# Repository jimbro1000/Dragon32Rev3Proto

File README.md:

# DRAGON 32 RECREATION Rev 3 #

This project started as a recreation of the SA2120 CPU Mainboard
for the 1982 Dragon Data **Dragon 32**

Everything (excluding modifications) is taken from the SA2120
schematics. Where this version changes is the move to surface
mount components which radically alters the size of each part
along with a move to using SRAM instead of DRAM. The intention
is that the board should be supplied fully or semi-populated
leaving just optional (socketed) components to be fitted.

The ROM is now a single 28C256 eprom with an option to switch
between two images using JP6 or to allow the rom to be
automatically selected from the PIA. In effect this allows the
computer to operate as a D32 but with two different images or
as a D64.

The video circuits have been isolated from the rest of the
board to improve output quality.

To maintain compatibility with the D64 there is an optional
serial port. This needs to be enabled by bridging a solder
jumper (JP3) to position 1-2. If the serial port is not
being populated it should be position 2-3. By default this
is not bridged and the computer will not function without
the jumper being set. If the supporting SMD ICs at U13 and
U14 are fitted the jumper can safely be left in position
1-2 regardless of whether the 6551 UART chip is fitting.

If you are fitting the board into an
early D32 case the serial port would be completely covered
without modifying the case. Later D32 cases had all four
ports but the fourth (serial) port blanked off internally.

A second (internal) cartridge port has been added, by way of
a 2x20 header, along with an additional +5V/Gnd pickup point
for further internal expansion. The keyboard connector also
has two additional pins that can supply 5v to the keyboard,
the extra pins are on the left. The keyboard should always 
be fitted to the right to avoid any shorts.

The board incorporates a replacement to the SAM chip based on
Ciaran Anscomb's SAMx4 design which in turn includes Stewart
Orchards 256k banker board 
<https://gitlab.com/sorchard001/dragon-256k-banker-board>

A custom VHDL is needed for this. Do not use the code from
Ciaran's site as it won't work.

The VHDL has potential (untried as of yet) to allow the
board to run permanently at double speed without loss of
a working display. The potential extends to running at 4x
speed but this is subject to using a suitable CPU and SRAM.

Because all of the CPU speed control is managed by the CPLD
replacing the SAM it is possible to change and update the
VHDL programming to include new features provided they do
not need changes to the board itself. Running at x4 speed
would require a different oscillator at X1 but would not
need other changes. All of the specified components are 
modern high performance equivalents and should be easily
able to cope with the high clock frequencies.

The board also includes three PIAs but only the first two are
necessary for normal usage. The third PIA (U7) is used by some
of the video daughterboards to provide additional functionality
such as a programmable character "rom".

All of the PIAs are changed to the W65C21 chip instead of the
MC6821. These chips work at higher frequencies and conveniently
use a smaller PLCC package

## Progress ##

In the current state (3.0) only the basics of the board have
been tested and proven. 

To be tested:

* SRAM conversion
* Serial port
* PIA 3
* SAMx4

## Modifications ##

### Joysticks ###

The two joystick ports provide a second fire button capability
wired to consecutive keyboard rows, as per the Tandy CoCo.
Unless a two button joystick is used this make no difference to
the operation of the computer. It also requires the use of 6-pin
DIN sockets, these are pin compatible with the 5-pin originals
so a regular single button joystick can still be used.

The two extra buttons can also be disabled by omitting L3 and L4.

### Parallel Port ###

A jumper (JP2) has been introduced to bypass the logic inverter
on the STROBE line. When bypassed the parallel port should
operate as a communication port for DRIVEWIRE.

### Memory Addressing ###

The board is configurable between 32k and 64k ram addressing
using jumper JP1. In most scenarios there is no reason to
disable the 64k option.

### Video PIA ###

One of the possible features of the board is to support an
extended version of the video circuitry to include 
external character ram. Adding a third PIA to the board takes
a little refinement of how PIAs are interfaced. In this case
the mapped memory for PIA1 is broken into 8 blocks, this first
maps to the original memory space for PIA1 while the other 7 
are effectively available to more registers. On this board
only the first of those 7 is used (yet). This makes addresses
$FF44-$FF47 map to the new PIA (referenced here as 1b).

Register A of PIA1b is control of additional functions  
bit 0 controls internal or external character image generation  
bit 1 controls automatic invert on bit 6 of the data bus  
bit 2 is manual control of the invert signal  
bit 3 controls automatic semigraphics on bit 7 of the data bus  
bit 4 is manual control of the semigraphics signal  
bit 5 opens the external character ram to writing  
bit 6 is a clock trigger to the external character ram address  
bit 7 is unused (proposed to be CoCo compatibility switch for 
the keyboard)  

Register B of PIA1b is used for programming the external
character ram data.

The external character ram can only be programmed while the
video is set to the internal character data of the 6847.

### Serial Port ###

The board includes the serial port capability originally
added to the D64. This adds a dedicated 6551 UART chip
to the machine allowing serial communications at higher
speeds without locking out the CPU. The port is optional.

To allow this to work the board *must* user a D64 power
board that supplies -12V instead of -5V. It is possible
to rig the board to work by bridging two pins (2 and 3)
of REG1 but this is not the intended mode of operation.
If the board is rigged for -5V supply then REG1, C18
and C19 must be left unpopulated.

## Substitutions ##

All of the components specified with the exception of
the CPU are current and should be readily available.
Supplies of 6809 CPUs are still plentiful but are all
NOS.

The Hitachi HD6309 is usable but may cause crashes in 
some software due to lazy coding. It is however still 
made thanks to usage in old military equipment in at
least one country.

### The Future ###

The board may look empty in its current form but the design
is dominated by the main data and address busses.

The design will also include two AY8912 audio chips to 
provide stereo sound. This brings utilisation of the 
additional device addressing to 50% but also fills up
the remainder of the board.

It is possible to increase the size of the board along
the bottom edge as the current design complies with the
original D32 design rather than the enlarged D64 board.

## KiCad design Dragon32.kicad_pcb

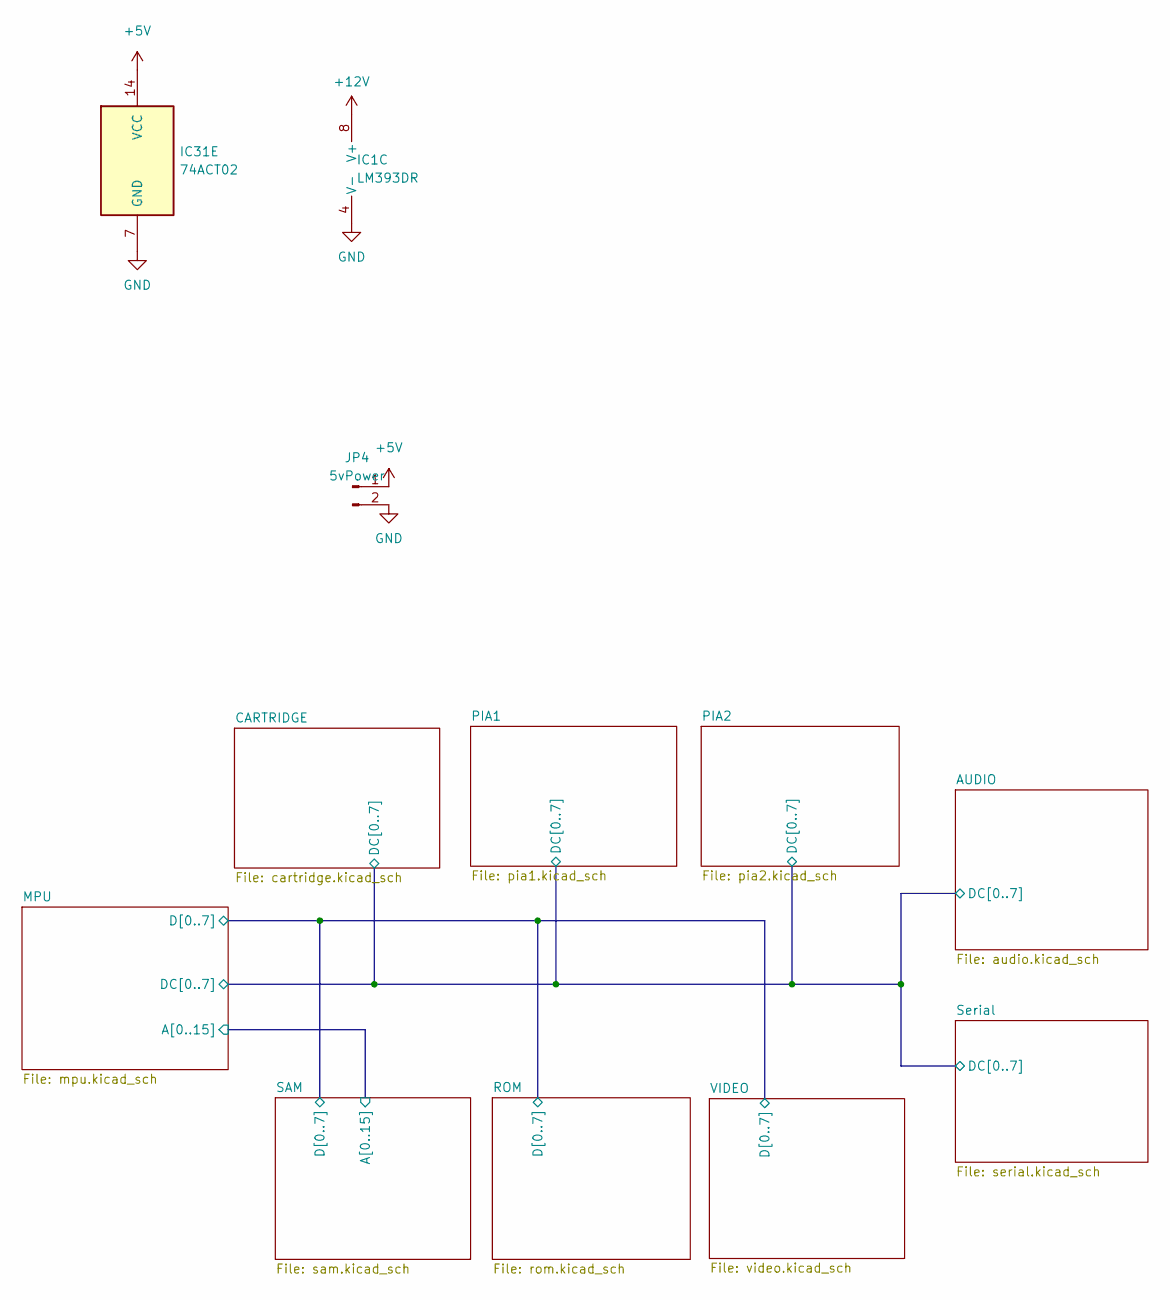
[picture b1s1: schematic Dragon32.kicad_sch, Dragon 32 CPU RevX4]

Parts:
IC1: LM393DR; SOP-8_3.9x4.9mm_P1.27mm; DigiKey 296-1015-1-ND
IC31: 74ACT02; SOIC-14_3.9x8.7mm_P1.27mm; DigiKey MC74ACT02DR2GOSCT-ND
JP4: 5vPower; PinHeader_1x02_P2.54mm_Vertical

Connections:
+12V: IC1.8 (V+); also elsewhere on the board

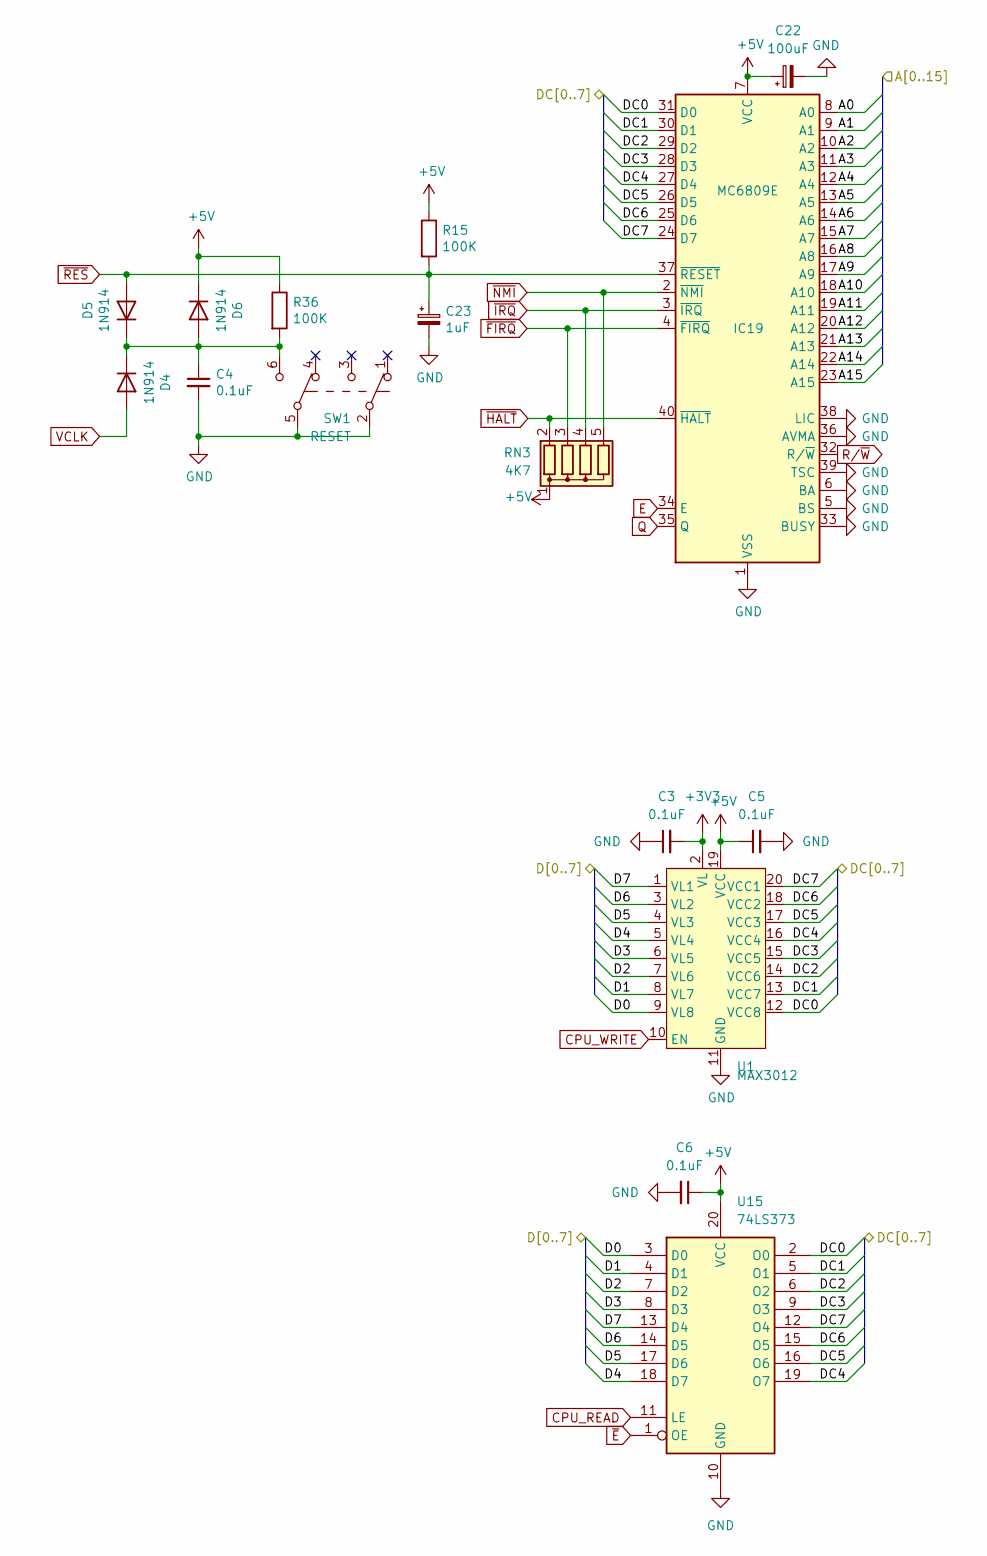
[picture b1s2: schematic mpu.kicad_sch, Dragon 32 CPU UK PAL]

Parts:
C3, C5, C6: 0.1uF; C_0805_2012Metric_Pad1.18x1.45mm_HandSolder; DigiKey 399-C0805C104K4RAC7800CT-ND
C4: 0.1uF; C_0805_2012Metric_Pad1.18x1.45mm_HandSolder; DigiKey BC1101CT-ND
C22: 100uF; CP_Elec_5x5.3; DigiKey 732-8598-1-ND
C23: 1uF; CP_Elec_4x4.5; DigiKey 732-8541-1-ND
D4, D5, D6: 1N914; D_SOD-323_HandSoldering; DigiKey 1N914FS-ND
IC19: MC6809E; DIP-40_W15.24mm
R15, R36: 100K; R_0805_2012Metric_Pad1.20x1.40mm_HandSolder; DigiKey CF14JT100KCT-ND
RN3: 4K7; R_Array_SIP5
SW1: RESET; Button_AlpsAlpine_SPUN190900; DigiKey 401-1225-ND
U1: MAX3012; TSSOP-20_4.4x6.5mm_P0.65mm; DigiKey MAX3012EUP+-ND
U15: 74LS373; SOIC-20W_7.5x12.8mm_P1.27mm

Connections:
/AUDIO/DC0: IC19.31 (D0), U1.12 (VCC8), U15.2 (O0); also elsewhere on the board
/AUDIO/DC1: IC19.30 (D1), U1.13 (VCC7), U15.5 (O1); also elsewhere on the board
/AUDIO/DC2: IC19.29 (D2), U1.14 (VCC6), U15.6 (O2); also elsewhere on the board
/AUDIO/DC3: IC19.28 (D3), U1.15 (VCC5), U15.9 (O3); also elsewhere on the board
/AUDIO/DC4: IC19.27 (D4), U1.16 (VCC4), U15.19 (O7); also elsewhere on the board
/AUDIO/DC5: IC19.26 (D5), U1.17 (VCC3), U15.16 (O6); also elsewhere on the board
/AUDIO/DC6: IC19.25 (D6), U1.18 (VCC2), U15.15 (O5); also elsewhere on the board
/AUDIO/DC7: IC19.24 (D7), U1.20 (VCC1), U15.12 (O4); also elsewhere on the board
/MPU/A0: IC19.8 (A0); also elsewhere on the board
/MPU/A1: IC19.9 (A1); also elsewhere on the board
/MPU/A2: IC19.10 (A2); also elsewhere on the board
/MPU/A3: IC19.11 (A3); also elsewhere on the board
/MPU/A4: IC19.12 (A4); also elsewhere on the board
/MPU/A5: IC19.13 (A5); also elsewhere on the board
/MPU/A6: IC19.14 (A6); also elsewhere on the board
/MPU/A7: IC19.15 (A7); also elsewhere on the board
/MPU/A13: IC19.21 (A13); also elsewhere on the board
/MPU/A14: IC19.22 (A14); also elsewhere on the board
/MPU/A15: IC19.23 (A15); also elsewhere on the board
/MPU/D0: U1.9 (VL8), U15.3 (D0); also elsewhere on the board
/MPU/D1: U1.8 (VL7), U15.4 (D1); also elsewhere on the board
/MPU/D2: U1.7 (VL6), U15.7 (D2); also elsewhere on the board
/MPU/D3: U1.6 (VL5), U15.8 (D3); also elsewhere on the board
/MPU/D5: U1.4 (VL3), U15.17 (D6); also elsewhere on the board
CPU_READ: U15.11 (LE); also elsewhere on the board
CPU_WRITE: U1.10 (EN); also elsewhere on the board
E: IC19.34 (E); also elsewhere on the board
unnamed: C4.1, D4.1 (K), D5.1 (K), D6.2 (A), R36.2, SW1.6 (C)
Q: IC19.35 (Q); also elsewhere on the board
R/~W: IC19.32 (R/~W); also elsewhere on the board
VCLK: D4.2 (A); also elsewhere on the board
~E: U15.1 (OE); also elsewhere on the board
~FIRQ: IC19.4 (~FIRQ), RN3.3 (R2); also elsewhere on the board
~HALT: IC19.40 (~HALT), RN3.2 (R1); also elsewhere on the board
~IRQ: IC19.3 (~IRQ), RN3.4 (R3); also elsewhere on the board
~NMI: IC19.2 (~NMI), RN3.5 (R4); also elsewhere on the board
~RES: C23.1, D5.2 (A), IC19.37 (~RESET), R15.2; also elsewhere on the board

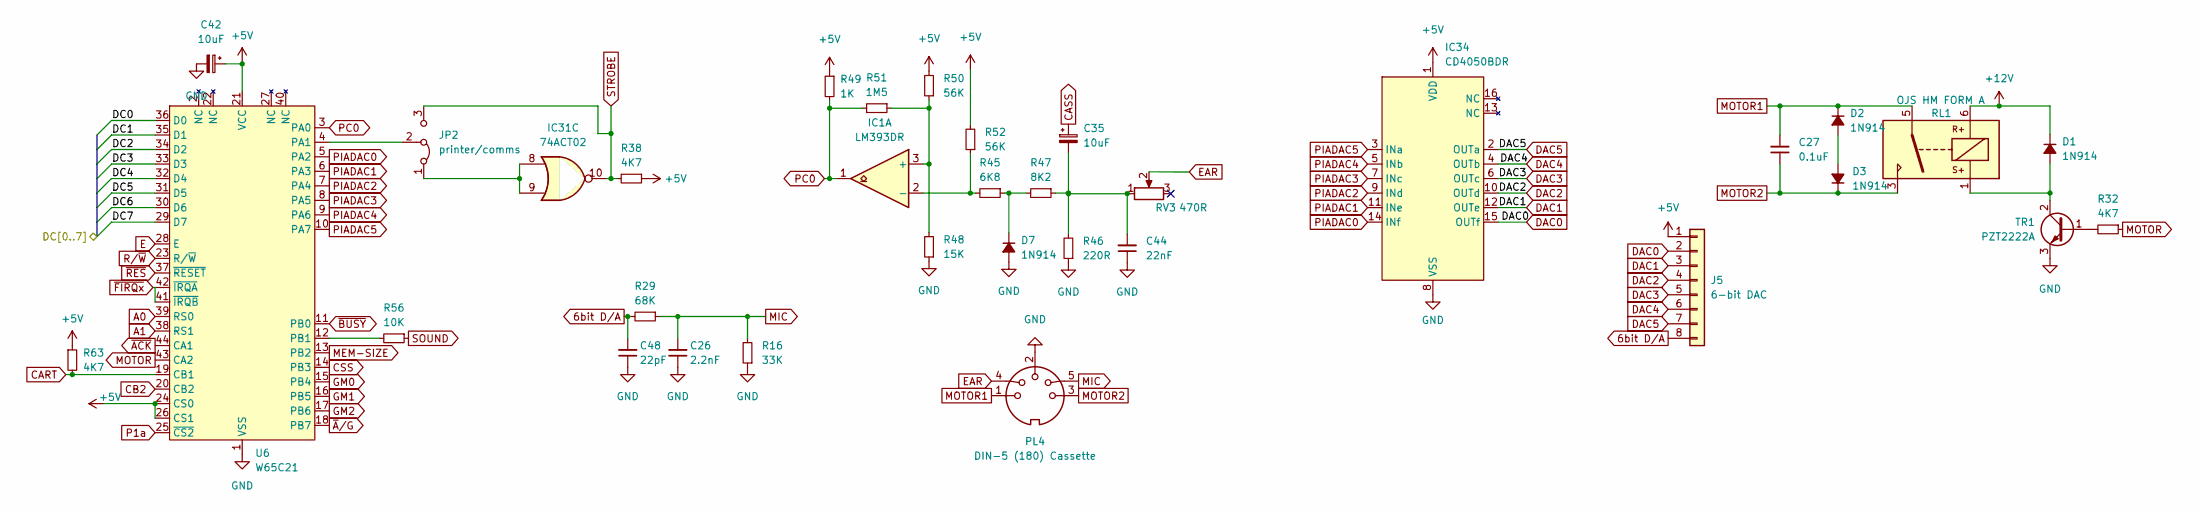
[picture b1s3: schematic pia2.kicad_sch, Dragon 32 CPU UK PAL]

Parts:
C26: 2.2nF; C_0805_2012Metric_Pad1.18x1.45mm_HandSolder; DigiKey BC1074CT-ND
C27: 0.1uF; C_0805_2012Metric_Pad1.18x1.45mm_HandSolder; DigiKey BC1101CT-ND
C35, C42: 10uF; CP_Elec_5x5.3; DigiKey 732-8593-1-ND
C44: 22nF; C_0805_2012Metric_Pad1.18x1.45mm_HandSolder; DigiKey BC2677CT-ND
C48: 22pF; C_0805_2012Metric_Pad1.18x1.45mm_HandSolder; DigiKey 399-13930-1-ND
D1, D2, D3, D7: 1N914; D_SOD-323_HandSoldering; DigiKey 1N914FS-ND
IC1: LM393DR; SOP-8_3.9x4.9mm_P1.27mm; DigiKey 296-1015-1-ND
IC31: 74ACT02; SOIC-14_3.9x8.7mm_P1.27mm; DigiKey MC74ACT02DR2GOSCT-ND
IC34: CD4050BDR; SOIC-16W_7.5x10.3mm_P1.27mm; DigiKey 296-31503-1-ND
J5: 6-bit DAC; PinSocket_1x08_P2.54mm_Vertical
JP2: printer/comms; PinHeader_1x03_P2.54mm_Vertical
PL4: DIN-5 (180) Cassette; DIN-5_DELTRON_671-0501_45deg_Horizontal
R16: 33K; R_0805_2012Metric_Pad1.20x1.40mm_HandSolder; DigiKey CF14JT33K0CT-ND
R29: 68K; R_0805_2012Metric_Pad1.20x1.40mm_HandSolder; DigiKey CF14JT68K0CT-ND
R32, R38, R63: 4K7; R_0805_2012Metric_Pad1.20x1.40mm_HandSolder; DigiKey CF14JT4K70CT-ND
R45: 6K8; R_0805_2012Metric_Pad1.20x1.40mm_HandSolder; DigiKey CF14JT6K80CT-ND
R46: 220R; R_0805_2012Metric_Pad1.20x1.40mm_HandSolder; DigiKey CF14JT220RCT-ND
R47: 8K2; R_0805_2012Metric_Pad1.20x1.40mm_HandSolder; DigiKey CF14JT8K20CT-ND
R48: 15K; R_0805_2012Metric_Pad1.20x1.40mm_HandSolder; DigiKey CF14JT15K0CT-ND
R49: 1K; R_0805_2012Metric_Pad1.20x1.40mm_HandSolder; DigiKey CF14JT1K00CT-ND
R50, R52: 56K; R_0805_2012Metric_Pad1.20x1.40mm_HandSolder; DigiKey CF14JT56K0CT-ND
R51: 1M5; R_0805_2012Metric_Pad1.20x1.40mm_HandSolder; DigiKey CF14JT1M50CT-ND
R56: 10K; R_0805_2012Metric_Pad1.20x1.40mm_HandSolder; DigiKey CF14JT10K0CT-ND
RL1: OJS HM FORM A; OJS HM 10A Relay; DigiKey 41-OJS-SH-105HMF,00000-ND
RV3: 470R; Potentiometer_Bourns_3386X_Horizontal; DigiKey 3386H-103LF-ND
TR1: PZT2222A; SOT-223-3_TabPin2
U6: W65C21; PLCC-44_SMD-Socket

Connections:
+12V: D1.1 (K), RL1.6; also elsewhere on the board
/AUDIO/DC0: U6.36 (D0); also elsewhere on the board
/AUDIO/DC1: U6.35 (D1); also elsewhere on the board
/AUDIO/DC2: U6.34 (D2); also elsewhere on the board
/AUDIO/DC3: U6.33 (D3); also elsewhere on the board
/AUDIO/DC4: U6.32 (D4); also elsewhere on the board
/AUDIO/DC5: U6.31 (D5); also elsewhere on the board
/AUDIO/DC6: U6.30 (D6); also elsewhere on the board
/AUDIO/DC7: U6.29 (D7); also elsewhere on the board
A0: U6.39 (RS0); also elsewhere on the board
A1: U6.38 (RS1); also elsewhere on the board
CART: R63.2, U6.19 (CB1); also elsewhere on the board
CB2: U6.20 (CB2); also elsewhere on the board
CSS: U6.14 (PB3); also elsewhere on the board
DAC0: IC34.15 (OUTf), J5.2
DAC1: IC34.12 (OUTe), J5.3
DAC2: IC34.10 (OUTd), J5.4
DAC3: IC34.6 (OUTc), J5.5
DAC4: IC34.4 (OUTb), J5.6
DAC5: IC34.2 (OUTa), J5.7
E: U6.28 (E); also elsewhere on the board
EAR: PL4.4, RV3.2
GM0: U6.15 (PB4); also elsewhere on the board
GM1: U6.16 (PB5); also elsewhere on the board
GM2: U6.17 (PB6); also elsewhere on the board
MEM-SIZE: U6.13 (PB2)
MIC: C26.2, PL4.5, R16.2, R29.1
MOTOR: R32.1, U6.43 (CA2)
MOTOR1: C27.2, D2.1 (K), PL4.1, RL1.5
MOTOR2: C27.1, D3.1 (K), PL4.3, RL1.3
unnamed: C35.2, C44.2, R46.2, R47.1, RV3.1
unnamed: D1.2 (A), RL1.1, TR1.2 (C)
unnamed: D2.2 (A), D3.2 (A)
unnamed: D7.1 (K), R45.1, R47.2
unnamed: IC1.3 (+), R48.2, R50.1, R51.1
unnamed: IC1.2 (-), R45.2, R52.1
unnamed: IC31.8, IC31.9, JP2.1 (A)
unnamed: JP2.2 (C), U6.4 (PA1)
unnamed: R32.2, TR1.1 (B)
unnamed: R56.2, U6.12 (PB1)
OUT_L: R56.1; also elsewhere on the board
P1a: U6.25 (~CS2); also elsewhere on the board
PC0: IC1.1, R49.2, R51.2, U6.3 (PA0)
PIADAC0: IC34.14 (INf), U6.5 (PA2)
PIADAC1: IC34.11 (INe), U6.6 (PA3)
PIADAC2: IC34.9 (INd), U6.7 (PA4)
PIADAC3: IC34.7 (INc), U6.8 (PA5)
PIADAC4: IC34.5 (INb), U6.9 (PA6)
PIADAC5: IC34.3 (INa), U6.10 (PA7)
R/~W: U6.23 (R/~W); also elsewhere on the board
STROBE: IC31.10, JP2.3 (B), R38.2; also elsewhere on the board
~ACK: U6.44 (CA1); also elsewhere on the board
~A/G: U6.18 (PB7); also elsewhere on the board
~BUSY: U6.11 (PB0); also elsewhere on the board
~FIRQx: U6.41 (~IRQB), U6.42 (~IRQA); also elsewhere on the board
~RES: U6.37 (~RESET); also elsewhere on the board

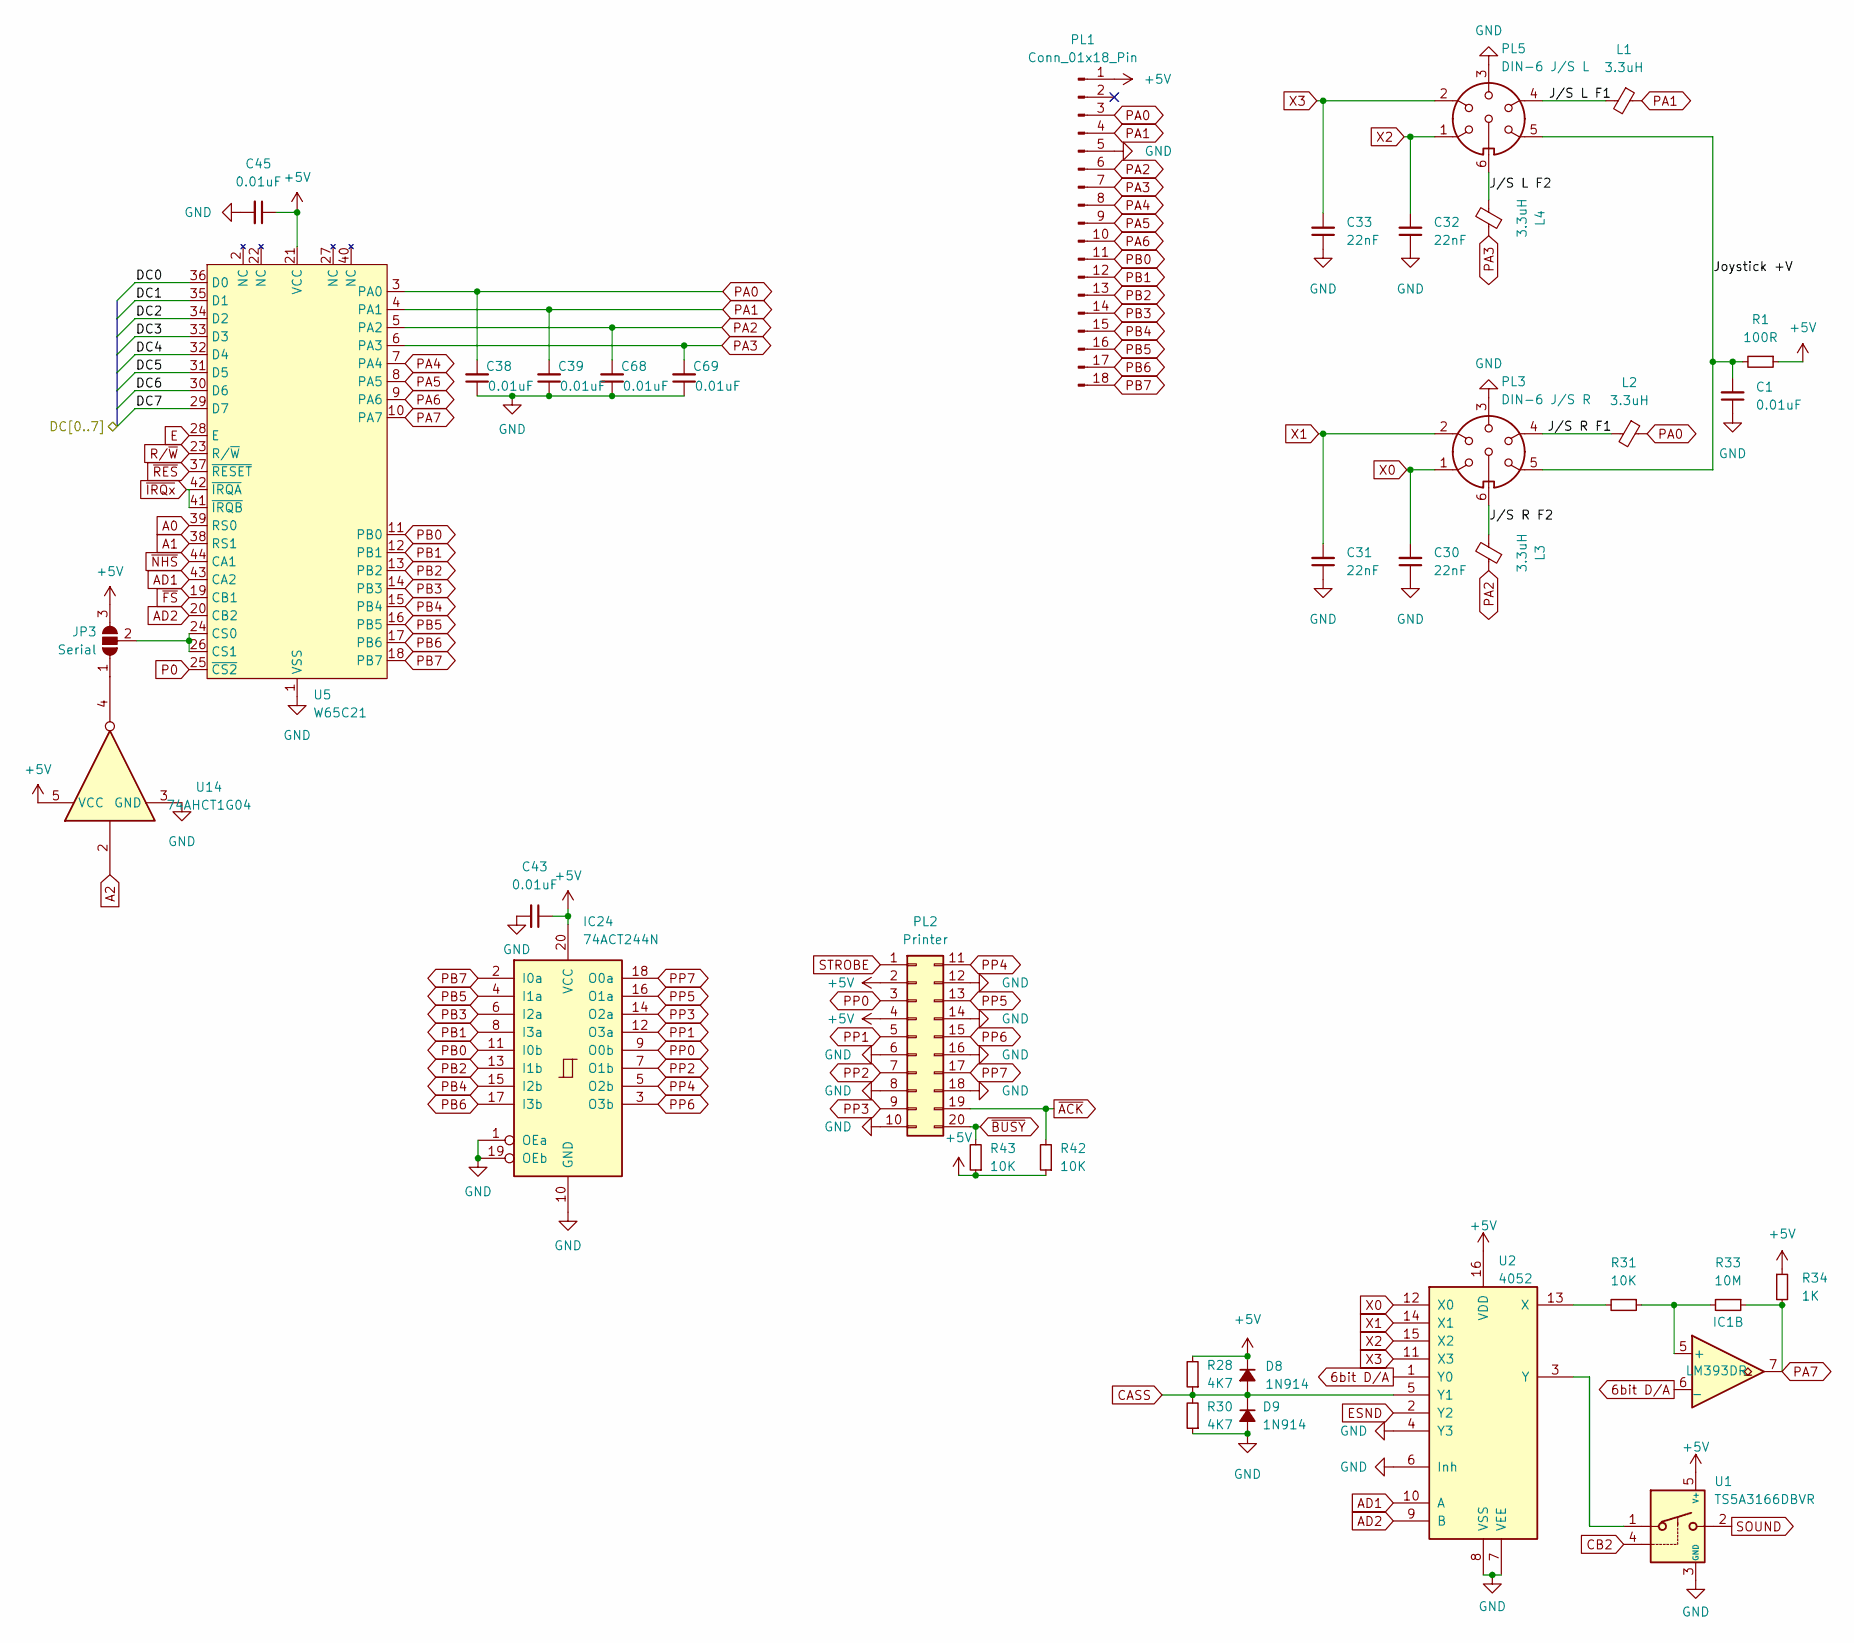
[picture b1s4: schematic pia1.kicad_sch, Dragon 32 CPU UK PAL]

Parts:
C1, C43, C45: 0.01uF; C_0805_2012Metric_Pad1.18x1.45mm_HandSolder; DigiKey BC2662CT-ND
C30, C31, C32, C33: 22nF; C_0805_2012Metric_Pad1.18x1.45mm_HandSolder; DigiKey BC2677CT-ND
C38, C39, C68, C69: 0.01uF; C_0805_2012Metric_Pad1.18x1.45mm_HandSolder; DigiKey BC1101CT-ND
D8, D9: 1N914; D_SOD-323_HandSoldering; DigiKey 1N914FS-ND
IC1: LM393DR; SOP-8_3.9x4.9mm_P1.27mm; DigiKey 296-1015-1-ND
IC24: 74ACT244N; SOIC-20W_7.5x12.8mm_P1.27mm; DigiKey 74ACT244SCXCT-ND
JP3: Serial; SolderJumper-3_P1.3mm_Open_Pad1.0x1.5mm
L1, L2, L3, L4: 3.3uH; L_1812_4532Metric_Pad1.30x3.40mm_HandSolder; DigiKey 495-5561-1-ND
PL1: Conn_01x18_Pin; PinHeader_1x18_P2.54mm_Vertical
PL2: Printer; IDC-Header_2x10-1MP_P2.54mm_Latch_Horizontal; DigiKey CHR20G-ND
PL3: DIN-6 J/S R; DIN-6_DELTRON_671-0601_Horizontal
PL5: DIN-6 J/S L; DIN-6_DELTRON_671-0601_Horizontal
R1: 100R; R_0805_2012Metric_Pad1.20x1.40mm_HandSolder; DigiKey CF14JT100RCT-ND
R28, R30: 4K7; R_0805_2012Metric_Pad1.20x1.40mm_HandSolder; DigiKey CF14JT4K70CT-ND
R31, R42, R43: 10K; R_0805_2012Metric_Pad1.20x1.40mm_HandSolder; DigiKey CF14JT10K0CT-ND
R33: 10M; R_0805_2012Metric_Pad1.20x1.40mm_HandSolder; DigiKey CF14JT10M0CT-ND
R34: 1K; R_0805_2012Metric_Pad1.20x1.40mm_HandSolder; DigiKey CF14JT1K00CT-ND
U1: TS5A3166DBVR; SOT-23-5
U2: 4052; TSSOP-16_4.4x5mm_P0.65mm
U5: W65C21; PLCC-44_SMD-Socket
U14: 74AHCT1G04; SOT-23-5_HandSoldering

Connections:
/AUDIO/DC0: U5.36 (D0); also elsewhere on the board
/AUDIO/DC1: U5.35 (D1); also elsewhere on the board
/AUDIO/DC2: U5.34 (D2); also elsewhere on the board
/AUDIO/DC3: U5.33 (D3); also elsewhere on the board
/AUDIO/DC4: U5.32 (D4); also elsewhere on the board
/AUDIO/DC5: U5.31 (D5); also elsewhere on the board
/AUDIO/DC6: U5.30 (D6); also elsewhere on the board
/AUDIO/DC7: U5.29 (D7); also elsewhere on the board
/MPU/D5: U1.4 (VL3); also elsewhere on the board
/PIA1/Joystick +V: C1.2, PL3.5, PL5.5, R1.2
/PIA1/J/S L F1: L1.2, PL5.4
/PIA1/J/S L F2: L4.2, PL5.6
/PIA1/J/S R F1: L2.2, PL3.4
/PIA1/J/S R F2: L3.2, PL3.6
A0: U5.39 (RS0); also elsewhere on the board
A1: U5.38 (RS1); also elsewhere on the board
A2: U14.2
E: U5.28 (E); also elsewhere on the board
unnamed: IC1.5 (+), R31.1, R33.2
unnamed: JP3.1 (A), U14.4
unnamed: JP3.2 (C), U5.24 (CS0), U5.26 (CS1)
P0: U5.25 (~CS2); also elsewhere on the board
PA0: C38.2, L2.1, PL1.3, U5.3 (PA0)
PA1: C39.2, L1.1, PL1.4, U5.4 (PA1)
PA2: C68.2, L3.1, PL1.6, U5.5 (PA2)
PA3: C69.2, L4.1, PL1.7, U5.6 (PA3)
PA4: PL1.8, U5.7 (PA4)
PA5: PL1.9, U5.8 (PA5)
PA6: PL1.10, U5.9 (PA6)
PA7: IC1.7, R33.1, R34.2, U5.10 (PA7)
PB0: IC24.11 (I0b), PL1.11, U5.11 (PB0)
PB1: IC24.8 (I3a), PL1.12, U5.12 (PB1)
PB2: IC24.13 (I1b), PL1.13, U5.13 (PB2)
PB3: IC24.6 (I2a), PL1.14, U5.14 (PB3)
PB4: IC24.15 (I2b), PL1.15, U5.15 (PB4)
PB5: IC24.4 (I1a), PL1.16, U5.16 (PB5)
PB6: IC24.17 (I3b), PL1.17, U5.17 (PB6)
PB7: IC24.2 (I0a), PL1.18, U5.18 (PB7)
PP0: IC24.9 (O0b), PL2.3
PP1: IC24.12 (O3a), PL2.5
PP2: IC24.7 (O1b), PL2.7
PP3: IC24.14 (O2a), PL2.9
PP4: IC24.5 (O2b), PL2.11
PP5: IC24.16 (O1a), PL2.13
PP6: IC24.3 (O3b), PL2.15
PP7: IC24.18 (O0a), PL2.17
R/~W: U5.23 (R/~W); also elsewhere on the board
STROBE: PL2.1; also elsewhere on the board
~ACK: PL2.19, R42.2; also elsewhere on the board
~BUSY: PL2.20, R43.2; also elsewhere on the board
~FS: U5.19 (CB1); also elsewhere on the board
~IRQx: U5.41 (~IRQB), U5.42 (~IRQA); also elsewhere on the board
~NHS: U5.44 (CA1); also elsewhere on the board
~RES: U5.37 (~RESET); also elsewhere on the board

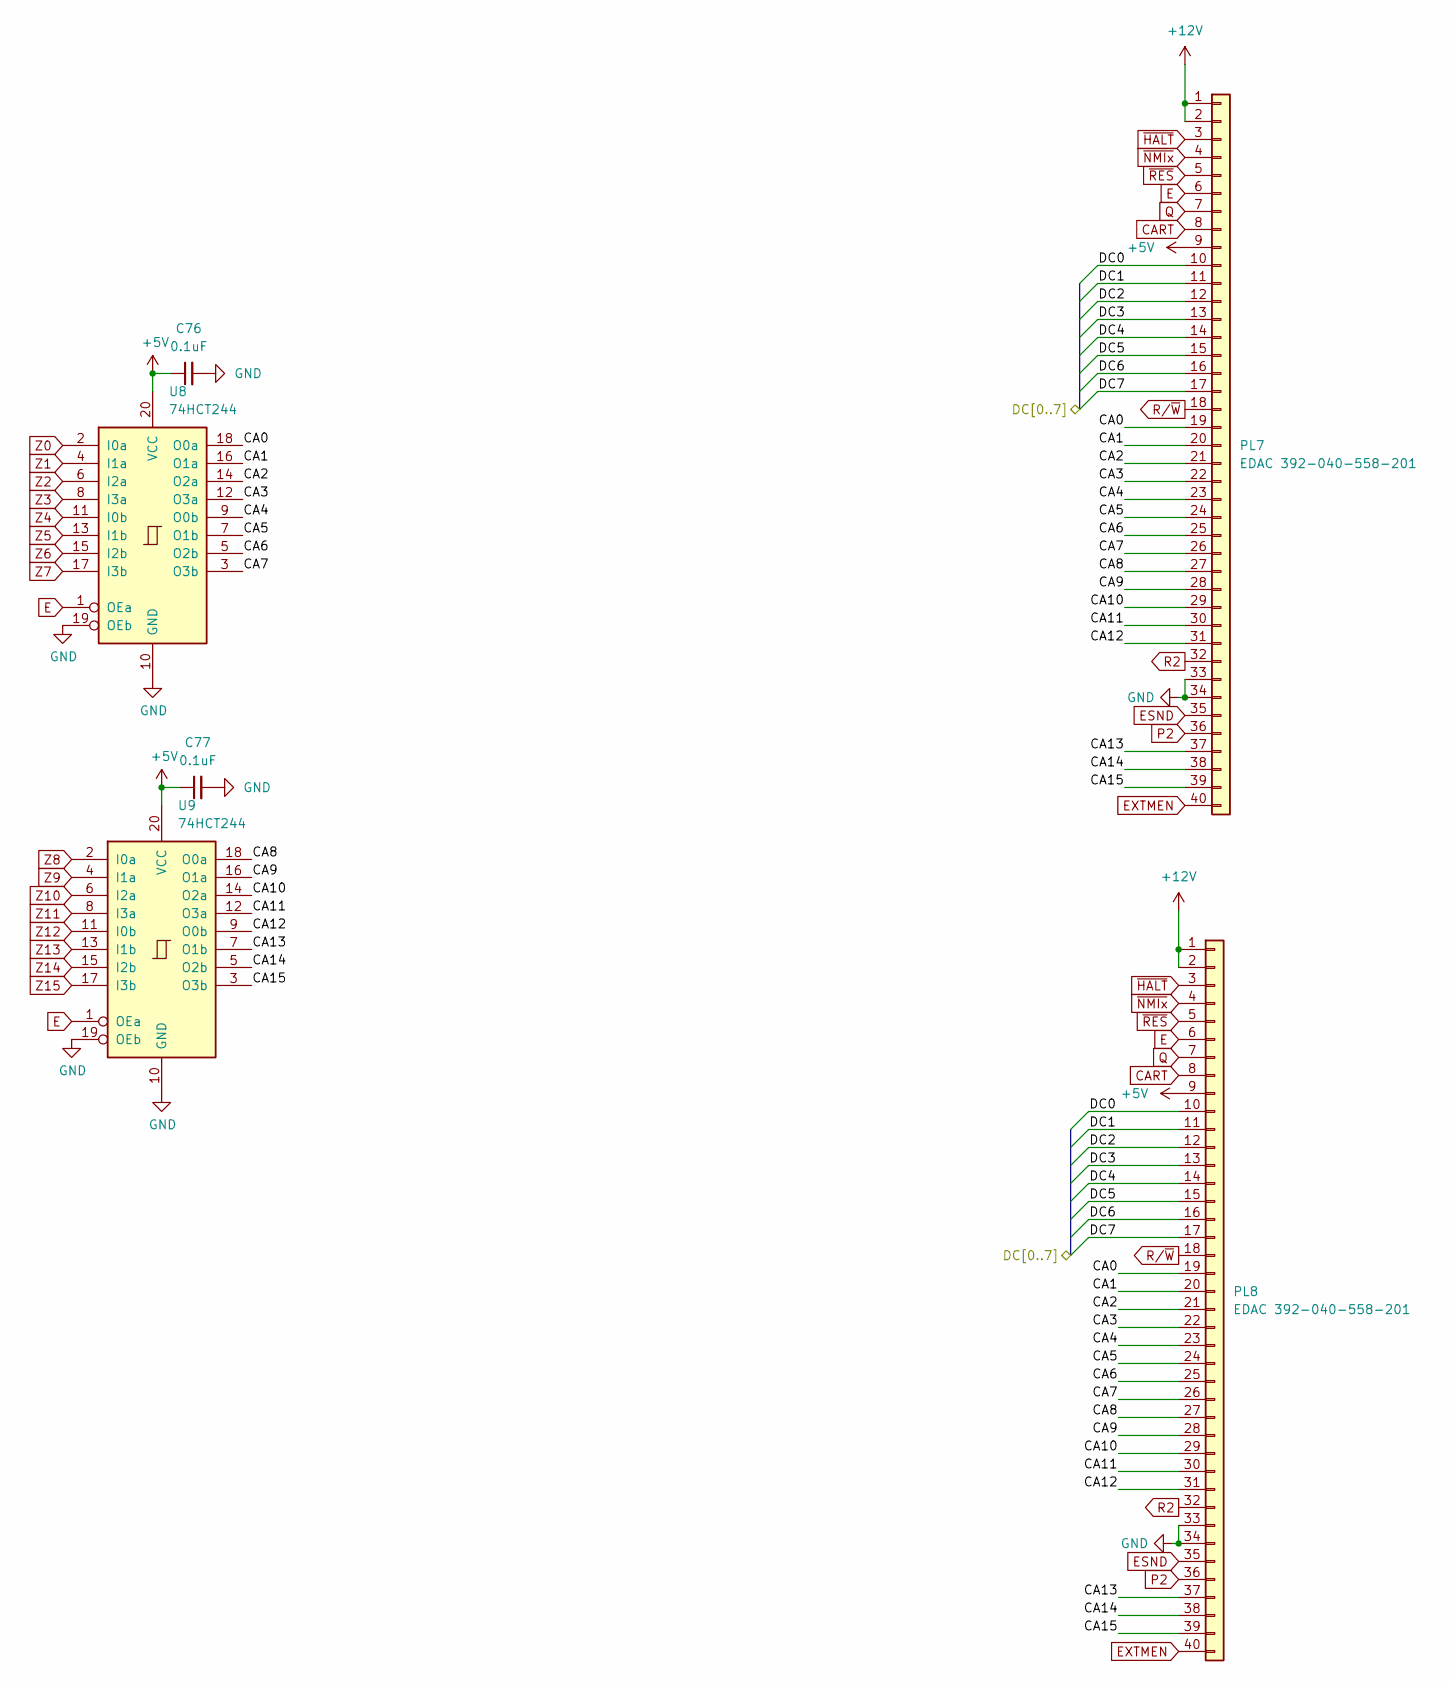
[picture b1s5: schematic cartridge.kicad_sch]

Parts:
C76, C77: 0.1uF; C_0805_2012Metric_Pad1.18x1.45mm_HandSolder; DigiKey 399-C0805C104K4RAC7800CT-ND
PL7: EDAC 392-040-558-201; PinHeader_2x20_P2.54mm_Vertical; DigiKey 151-395-040-558-201-ND
PL8: EDAC 392-040-558-201; Edge_2x20_P2.54mm_OvalMP; DigiKey 151-395-040-558-201-ND
U8, U9: 74HCT244; TSSOP-20_4.4x6.5mm_P0.65mm; DigiKey 296-8402-1-ND

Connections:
+12V: PL7.1, PL7.2, PL8.1, PL8.2; also elsewhere on the board
/AUDIO/DC0: PL7.10, PL8.10; also elsewhere on the board
/AUDIO/DC1: PL7.11, PL8.11; also elsewhere on the board
/AUDIO/DC2: PL7.12, PL8.12; also elsewhere on the board
/AUDIO/DC3: PL7.13, PL8.13; also elsewhere on the board
/AUDIO/DC4: PL7.14, PL8.14; also elsewhere on the board
/AUDIO/DC5: PL7.15, PL8.15; also elsewhere on the board
/AUDIO/DC6: PL7.16, PL8.16; also elsewhere on the board
/AUDIO/DC7: PL7.17, PL8.17; also elsewhere on the board
/CARTRIDGE/CA0: PL7.19, PL8.19, U8.18 (O0a)
/CARTRIDGE/CA1: PL7.20, PL8.20, U8.16 (O1a)
/CARTRIDGE/CA2: PL7.21, PL8.21, U8.14 (O2a)
/CARTRIDGE/CA3: PL7.22, PL8.22, U8.12 (O3a)
/CARTRIDGE/CA4: PL7.23, PL8.23, U8.9 (O0b)
/CARTRIDGE/CA5: PL7.24, PL8.24, U8.7 (O1b)
/CARTRIDGE/CA6: PL7.25, PL8.25, U8.5 (O2b)
/CARTRIDGE/CA7: PL7.26, PL8.26, U8.3 (O3b)
/CARTRIDGE/CA8: PL7.27, PL8.27, U9.18 (O0a)
/CARTRIDGE/CA9: PL7.28, PL8.28, U9.16 (O1a)
/CARTRIDGE/CA10: PL7.29, PL8.29, U9.14 (O2a)
/CARTRIDGE/CA11: PL7.30, PL8.30, U9.12 (O3a)
/CARTRIDGE/CA12: PL7.31, PL8.31, U9.9 (O0b)
/CARTRIDGE/CA13: PL7.37, PL8.37, U9.7 (O1b)
/CARTRIDGE/CA14: PL7.38, PL8.38, U9.5 (O2b)
/CARTRIDGE/CA15: PL7.39, PL8.39, U9.3 (O3b)
CART: PL7.8, PL8.8; also elsewhere on the board
E: PL7.6, PL8.6, U8.1 (OEa), U9.1 (OEa); also elsewhere on the board
ESND: PL7.35, PL8.35; also elsewhere on the board
EXTMEN: PL7.40, PL8.40; also elsewhere on the board
P2: PL7.36, PL8.36; also elsewhere on the board
Q: PL7.7, PL8.7; also elsewhere on the board
R2: PL7.32, PL8.32; also elsewhere on the board
R/~W: PL7.18, PL8.18; also elsewhere on the board
Z0: U8.2 (I0a); also elsewhere on the board
Z1: U8.4 (I1a); also elsewhere on the board
Z2: U8.6 (I2a); also elsewhere on the board
Z3: U8.8 (I3a); also elsewhere on the board
Z4: U8.11 (I0b); also elsewhere on the board
Z5: U8.13 (I1b); also elsewhere on the board
Z6: U8.15 (I2b); also elsewhere on the board
Z7: U8.17 (I3b); also elsewhere on the board
Z8: U9.2 (I0a); also elsewhere on the board
Z9: U9.4 (I1a); also elsewhere on the board
Z10: U9.6 (I2a); also elsewhere on the board
Z11: U9.8 (I3a); also elsewhere on the board
Z12: U9.11 (I0b); also elsewhere on the board
Z13: U9.13 (I1b); also elsewhere on the board
Z14: U9.15 (I2b); also elsewhere on the board
Z15: U9.17 (I3b); also elsewhere on the board
~HALT: PL7.3, PL8.3; also elsewhere on the board
~NMIx: PL7.4, PL8.4; also elsewhere on the board
~RES: PL7.5, PL8.5; also elsewhere on the board

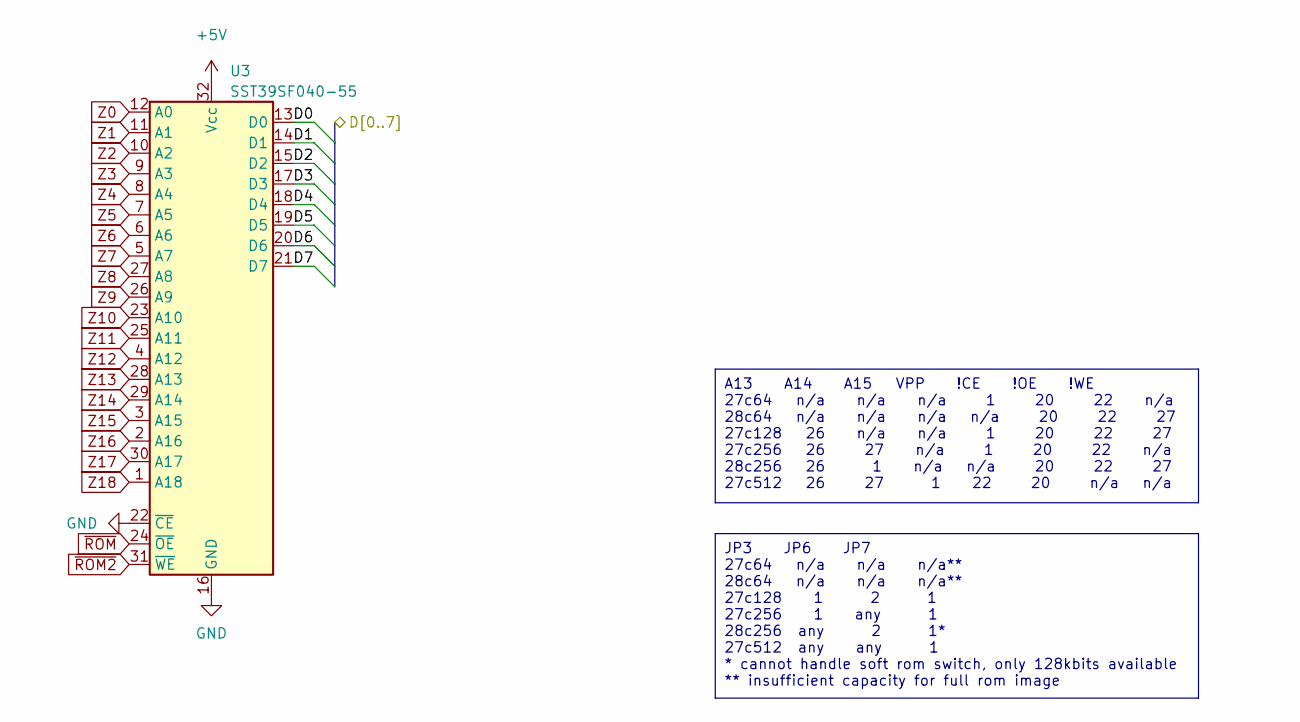
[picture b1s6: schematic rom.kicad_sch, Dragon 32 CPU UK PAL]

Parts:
U3: SST39SF040-55; PLCC-32_THT-Socket; DigiKey SST39SF040-55-4C-NHE-ND

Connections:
/MPU/D0: U3.13 (D0); also elsewhere on the board
/MPU/D1: U3.14 (D1); also elsewhere on the board
/MPU/D2: U3.15 (D2); also elsewhere on the board
/MPU/D3: U3.17 (D3); also elsewhere on the board
/MPU/D5: U3.19 (D5); also elsewhere on the board
Z0: U3.12 (A0); also elsewhere on the board
Z1: U3.11 (A1); also elsewhere on the board
Z2: U3.10 (A2); also elsewhere on the board
Z3: U3.9 (A3); also elsewhere on the board
Z4: U3.8 (A4); also elsewhere on the board
Z5: U3.7 (A5); also elsewhere on the board
Z6: U3.6 (A6); also elsewhere on the board
Z7: U3.5 (A7); also elsewhere on the board
Z8: U3.27 (A8); also elsewhere on the board
Z9: U3.26 (A9); also elsewhere on the board
Z10: U3.23 (A10); also elsewhere on the board
Z11: U3.25 (A11); also elsewhere on the board
Z12: U3.4 (A12); also elsewhere on the board
Z13: U3.28 (A13); also elsewhere on the board
Z14: U3.29 (A14); also elsewhere on the board
Z15: U3.3 (A15); also elsewhere on the board
Z16: U3.2 (A16); also elsewhere on the board
Z17: U3.30 (A17); also elsewhere on the board
Z18: U3.1 (A18); also elsewhere on the board
~ROM2: U3.31 (~WE)
~ROM: U3.24 (~OE)

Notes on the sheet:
JP3 JP6 JP7 27c64 n/a n/a n/a** 28c64 n/a n/a n/a** 27c128 1 2 1 27c256 1 any 1 28c256 any 2 1* 27c512 any any 1 * cannot handle soft rom switch, only 128kbits available ** insufficient capacity for full rom image
A13 A14 A15 VPP !CE !OE !WE 27c64 n/a n/a n/a 1 20 22 n/a 28c64 n/a n/a n/a n/a 20 22 27 27c128 26 n/a n/a 1 20 22 27 27c256 26 27 n/a 1 20 22 n/a 28c256 26 1 n/a n/a 20 22 27 27c512 26 27 1 22 20 n/a n/a
